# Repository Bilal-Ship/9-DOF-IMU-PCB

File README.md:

9-DOF IMU with Magnetometer — Custom KiCad PCB
Custom two-layer sensor PCB integrating a 6-axis inertial sensor and a 3-axis magnetometer over I²C.

> **Project status:** Schematic and PCB layout completed in KiCad 9. The latest documented PCB design-rules check reported **0 errors**, **0 unconnected items**, and **3 silkscreen warnings**. The board has **not been fabricated, assembled, powered, or bench-tested**. This repository documents a PCB design—not a demonstrated working physical device.
Quick overview
The board combines measurements from two sensor ICs:
Device	Function	Role in the design
ST LSM6DSO32X	3-axis accelerometer + 3-axis gyroscope	Six inertial sensing axes, including a selectable accelerometer full-scale range up to ±32 g
MEMSIC MMC5983MA	3-axis magnetometer	Three magnetic-field sensing axes
Together they provide nine sensing axes (3 acceleration + 3 angular velocity + 3 magnetic field). This is a 9-axis sensor board, not a board that already performs sensor fusion, attitude estimation, or navigation on its own. A separate host controller and firmware would be needed to acquire and process measurements.
Design environment: KiCad 9 · schematic capture · custom sensor symbols · two-layer PCB layout · copper zones · routing · design-rule checking.
Gallery
PCB 3D view

KiCad 3D render of the current design. The connector body does not appear in this rendering because its 3D model has not been attached; its footprint is present in the PCB design.
PCB routing and layer view

PCB Editor capture showing the routed board and copper regions. Visible silkscreen labels overlap in places, consistent with the three documented DRC warnings.
Electrical schematic
View the schematic PDF, or open the KiCad schematic source.
Design verification evidence

Both sensors are intended to share the I²C bus; the board contains pull-up resistors for the bus lines. The connector exposes the supply, ground, serial lines, and one inertial-sensor interrupt signal. The board does not contain an onboard microcontroller or firmware.
External interface (J1)
Pin	Label shown in the design	Function
1	`+3V3`	External regulated 3.3 V input
2	`GND`	Ground
3	`SDA`	I²C data
4	`SCL`	I²C clock
5	`IMU_INT1`	LSM6DSO32X interrupt routed to host
> Check pin numbering and orientation in the source PCB/footprint before connecting any hardware. A 3D connector body is not currently rendered.
Circuit design
Sensor selection
LSM6DSO32X: integrates a digital 3-axis accelerometer and 3-axis gyroscope. The device supports several programmable accelerometer ranges, with ±32 g as the maximum listed range. The board does not by itself configure the sensor to any one range; that would be done by host firmware.
MMC5983MA: adds three-axis magnetic-field sensing through a separate digital sensor IC.
Refer to the manufacturer datasheets for actual operating ranges, initialization procedures, I²C addresses, and recommended application circuits: references.
Power and decoupling
The design exposes the +3V3 rail through J1. It is intended to be supplied by an external, regulated 3.3 V source; no on-board 3.3 V regulator is shown in the documented schematic. Local capacitors are placed at sensor supply pins. The magnetometer's `CAP` connection includes a bulk capacitor (shown as 15 µF in the source design), supporting its internal SET/RESET circuitry; MEMSIC recommends a nearby low-ESR capacitor of at least 10 µF on this pin.
I²C and interrupts
The design includes SDA/SCL pull-ups to the 3.3 V rail and exports both lines on J1. The inertial sensor's `INT1` is routed out to the interface. An additional `INT2` signal is not exported on the documented 5-pin interface.
PCB layout
The board is laid out with two copper layers. Front and back copper are visible in the screenshots; the back layer contains a ground-filled region. Component placement, short local sensor support connections, via transitions, and the ground network were considered during routing.
Engineering debugging example
During PCB review, an apparently blue (ground) region did not necessarily mean every nearby GND pad was electrically connected. A region of ground copper was isolated by routing/clearance geometry. The final design was corrected by explicitly connecting the affected ground network around the decoupling capacitor, then refilling zones and rerunning DRC. This highlighted the difference between a visually present copper pour and an electrically connected ground net.
Verification and limitations
Check	Observed outcome	Interpretation
PCB DRC errors	0	No errors reported by the enabled DRC checks
Unconnected items	0	No unconnected items reported
DRC warnings	3	Two silkscreen references clipped by board edge (U2, J1); one overlap (C1)
Schematic-to-PCB parity	Not run in screenshot	This specific parity test is not claimed as passed
Ignored tests	5 listed	Not all possible tests were enabled
Fabrication / assembly	Not performed	Physical manufacturing not established
Power-up / signal tests	Not performed	Electrical or sensor performance not verified
Scope: This repository demonstrates schematic design, component integration, custom symbol handling, PCB layout, routing, and DRC-based verification. It does not claim tested noise performance, calibrated sensor outputs, sensor fusion, functional firmware, or hardware validation.
Repository structure
```text
9-DOF-IMU-PCB/
├── README.md
├── Hardware/
│   ├── 9 Axis IMU with a Magnetometer.kicad_pro
│   ├── 9 Axis IMU with a Magnetometer.kicad_sch
│   ├── 9 Axis IMU with a Magnetometer.kicad_pcb
│   ├── LSM6DSO32X.kicad_sym
│   ├── MMC5983MA.kicad_sym
│   └── sym-lib-table
├── Images/
│   ├── pcb-3d-front.png
│   ├── pcb-layout.png
│   └── drc-results.png
└── Docs/
    ├── schematic.pdf
    ├── design-notes.md
    └── references.md
```
Opening the design in KiCad
Install KiCad 9.
Clone or download this repository.
Open `Hardware/9 Axis IMU with a Magnetometer.kicad_pro` in KiCad.
Open the schematic and PCB from the KiCad project manager.
Confirm the project-local custom symbol libraries resolve and review the schematic against the PDF.
Run DRC yourself in PCB Editor using the project settings. For results directly comparable to the screenshot, review which checks are enabled, including parity.
Portability note: The design uses custom `.kicad_sym` libraries. `Hardware/sym-lib-table` should reference these with project-relative `${KIPRJMOD}` paths, not paths to the original creator's Windows account. Verify library paths before distributing the project; successful opening on the original computer alone does not prove portability to another computer.
Design decisions and background
See Design Notes for sensor interfaces, support circuitry, board layout, verification, engineering lessons, and next steps.
Further development (not yet completed)
Resolve or formally accept silkscreen warnings, particularly if fabricating the board.
Attach and check an appropriate 3D connector model and verify the actual connector footprint/pin orientation.
Validate project library portability on another computer.
Run schematic ERC and schematic-to-PCB parity checks, and investigate any issues found.
Manufacture and assemble a prototype.
Develop firmware to scan the I²C bus, initialize both sensors, and capture measurements.
Test power integrity, interrupts, I²C operation, orientation behavior, and calibration.
References
LSM6DSO32X — STMicroelectronics datasheet
MMC5983MA — MEMSIC datasheet
KiCad 9 documentation
---
Author: Bilal-Ship  
Project type: Personal hardware/PCB design portfolio project  
Status: Design completed; unmanufactured and untested

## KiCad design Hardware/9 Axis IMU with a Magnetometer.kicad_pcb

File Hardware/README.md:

KiCad schematic, PCB layout, project configuration, and custom sensor symbol libraries

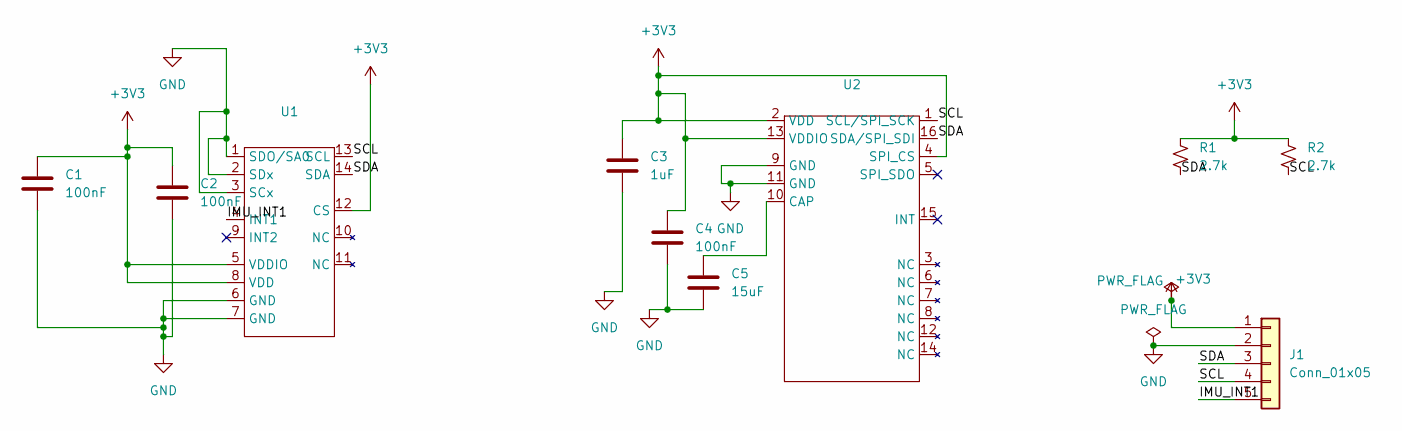
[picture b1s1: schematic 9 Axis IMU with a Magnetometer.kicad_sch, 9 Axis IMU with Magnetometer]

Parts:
C1, C2, C4: 100nF; C_0603_1608Metric
C3: 1uF; C_0603_1608Metric
C5: 15uF; C_0805_2012Metric
J1: Conn_01x05; JST_SH_SM05B-SRSS-TB_1x05-1MP_P1.00mm_Horizontal
R1, R2: 2.7k; R_0603_1608Metric
U1: LGA-14_3x2.5mm_P0.5mm_LayoutBorder3x4y
U2: LGA-16_3x3mm_P0.5mm

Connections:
+3V3: C1.1, C2.1, C3.1, C4.1, J1.1, R1.1, R2.1, U1.5 (VDDIO), U1.8 (VDD), U1.12 (CS), U2.2 (VDD), U2.4 (SPI_CS), U2.13 (VDDIO)
/IMU_INT1: J1.5, U1.4 (INT1)
/SCL: J1.4, R2.2, U1.13 (SCL), U2.1 (SCL/SPI_SCK)
/SDA: J1.3, R1.2, U1.14 (SDA), U2.16 (SDA/SPI_SDI)
GND: C1.2, C2.2, C3.2, C4.2, C5.2, J1.2, U1.1 (SDO/SA0), U1.2 (SDx), U1.3 (SCx), U1.6 (GND), U1.7 (GND), U2.9 (GND), U2.11 (GND)
unnamed: C5.1, U2.10 (CAP)

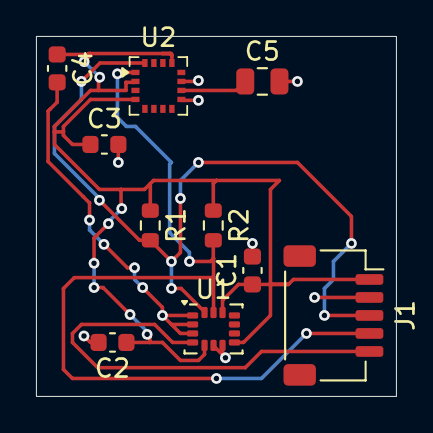
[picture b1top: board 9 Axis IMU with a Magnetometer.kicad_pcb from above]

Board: 2 copper layers, 20.0 x 20.0 mm, 10 parts (0 on the bottom side), 6 nets.
